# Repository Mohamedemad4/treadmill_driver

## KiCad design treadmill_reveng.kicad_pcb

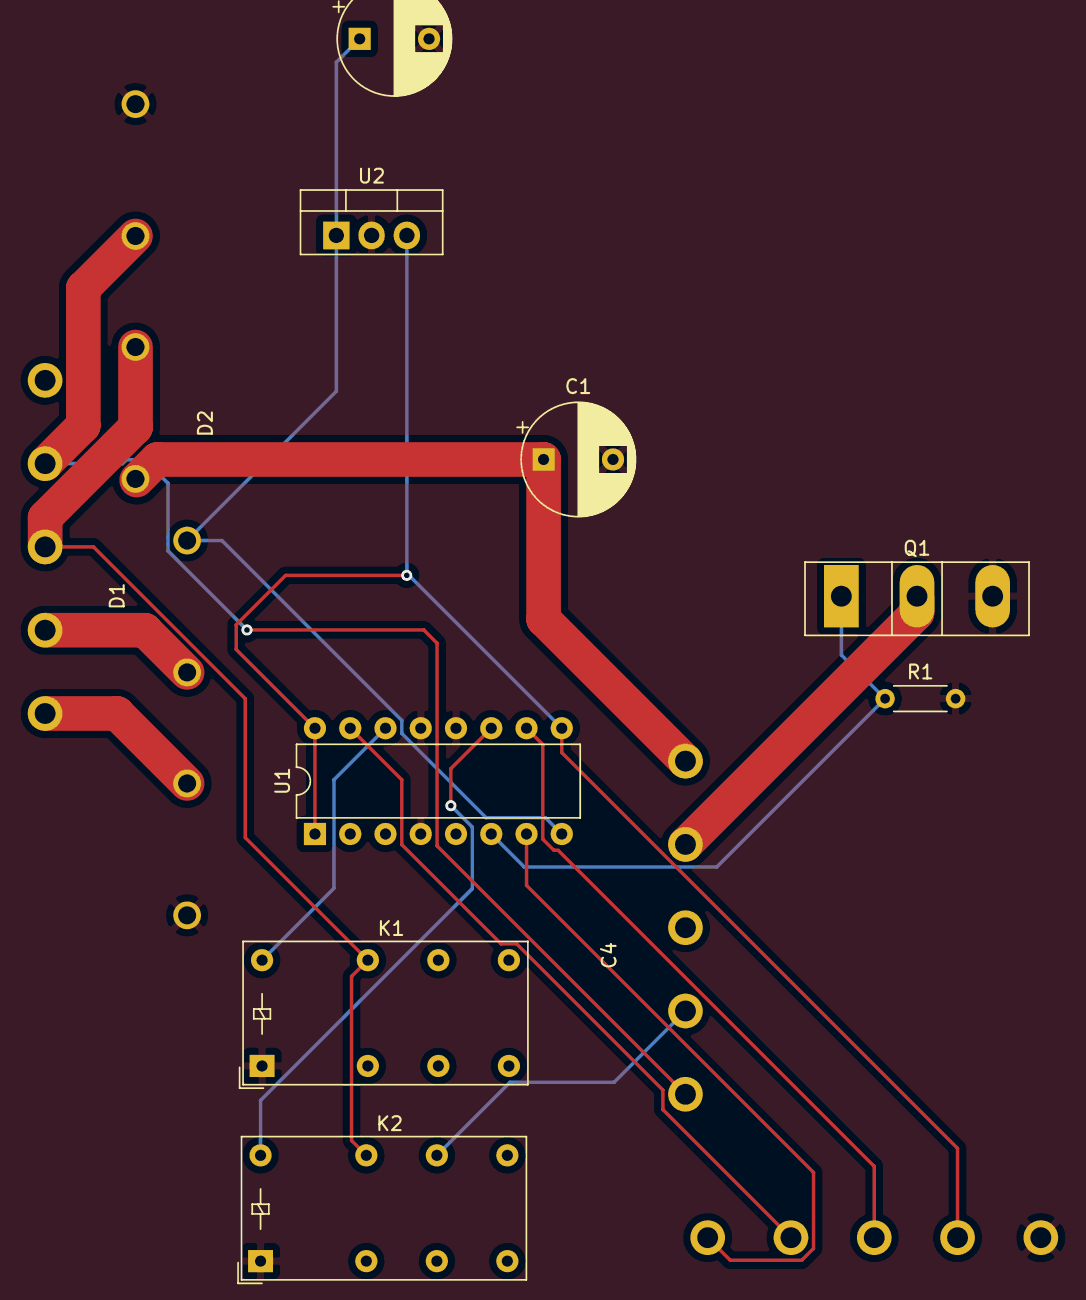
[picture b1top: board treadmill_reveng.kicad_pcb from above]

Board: 2 copper layers, 13 parts (0 on the bottom side), 16 nets.

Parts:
C1: 470uF; CP_Radial_D8.0mm_P5.00mm
C2: 150uF; CP_Radial_D8.0mm_P5.00mm
C3, C4, C5: 5mmScrewTerminal; Screw_terminal_5mm
D1, D2: GBJ5010-BP; GBJ5010
K1, K2: HK19F-5V-SHG; Relay_DPDT_Finder_30.22
Q1: IKW50N60H3; TO-247-3_Vertical
R1: 10k; R_Axial_DIN0204_L3.6mm_D1.6mm_P5.08mm_Horizontal
U1: L293D; DIP-16_W7.62mm
U2: L7805; TO-220-3_Vertical

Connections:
AC12vLive: C3.5, D1.3
AC12vN: C3.4, D1.2
AC220N: C3.2, C4.5, D2.3
AC220VLive: C3.3, D2.2, K1.21, K2.21
ACMotorRed: C4.4, K2.22
CONTROL_ACMotorBlack: C5.2, U1.15
CONTROL_ACMotorRed: C5.3, U1.10
CONTROL_DCMotorNegative: C5.1, U1.7
DC5v: C5.4, U1.1, U1.9, U1.16, U2.3
DC12Vpostive: C2.1, D1.1, U1.8, U2.1
DC220Vpostive: C1.1, C4.1, D2.1
DCGND: C1.2, C2.2, C5.5, D1.4, D2.4, K1.A1, K2.A1, Q1.3, R1.2, U1.4, U1.5, U1.12, U1.13, U2.2
DcMotorNegative: C4.2, Q1.2
unnamed: K1.A2, U1.14
unnamed: K2.A2, U1.11
unnamed: Q1.1, R1.1, U1.6

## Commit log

2020-12-16 init stuff
2020-12-16 added pull down resistor
2020-12-16 copper fill
2021-03-03 new netlist with correct sizes
2021-03-03 new placement
2021-03-03 rev2 routing
